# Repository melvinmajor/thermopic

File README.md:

# ThermoPIC

1st project of the academic year for the lesson of digital electronics 2nd Bachelor at EPHEC Louvain-la-Neuve

## Our Team

Our group number is: **1**

Our team is composed of 4 people :

- Melvin Campos Casares (_**@melvinmajor**_)
- Maxime De Cock (_**@maxicosi**_)
- Guillaume Vanden Herrewegen (_**@guivdh**_)
- Hubert Van De Walle (_**@HE201496**_)

We use Trello to manage our teamwork : [Trello - ThermoPic project](https://trello.com/b/enrK0mAl/thermopic-project).

## ThermoPIC

ThermoPIC is a project for the lesson of digital electronics.
In this project, we're working with the 18F458 PIC (High-Performance, Enhanced Flash Microcontrollers with CAN Module).
You will find some documentation inside the [doc](doc/) folder.

We're working with 2 programming languages :

- C
- Java

## License

This project is licensed under the GNU General Public License v3.0 - see the [LICENSE](LICENSE.md) file for details.

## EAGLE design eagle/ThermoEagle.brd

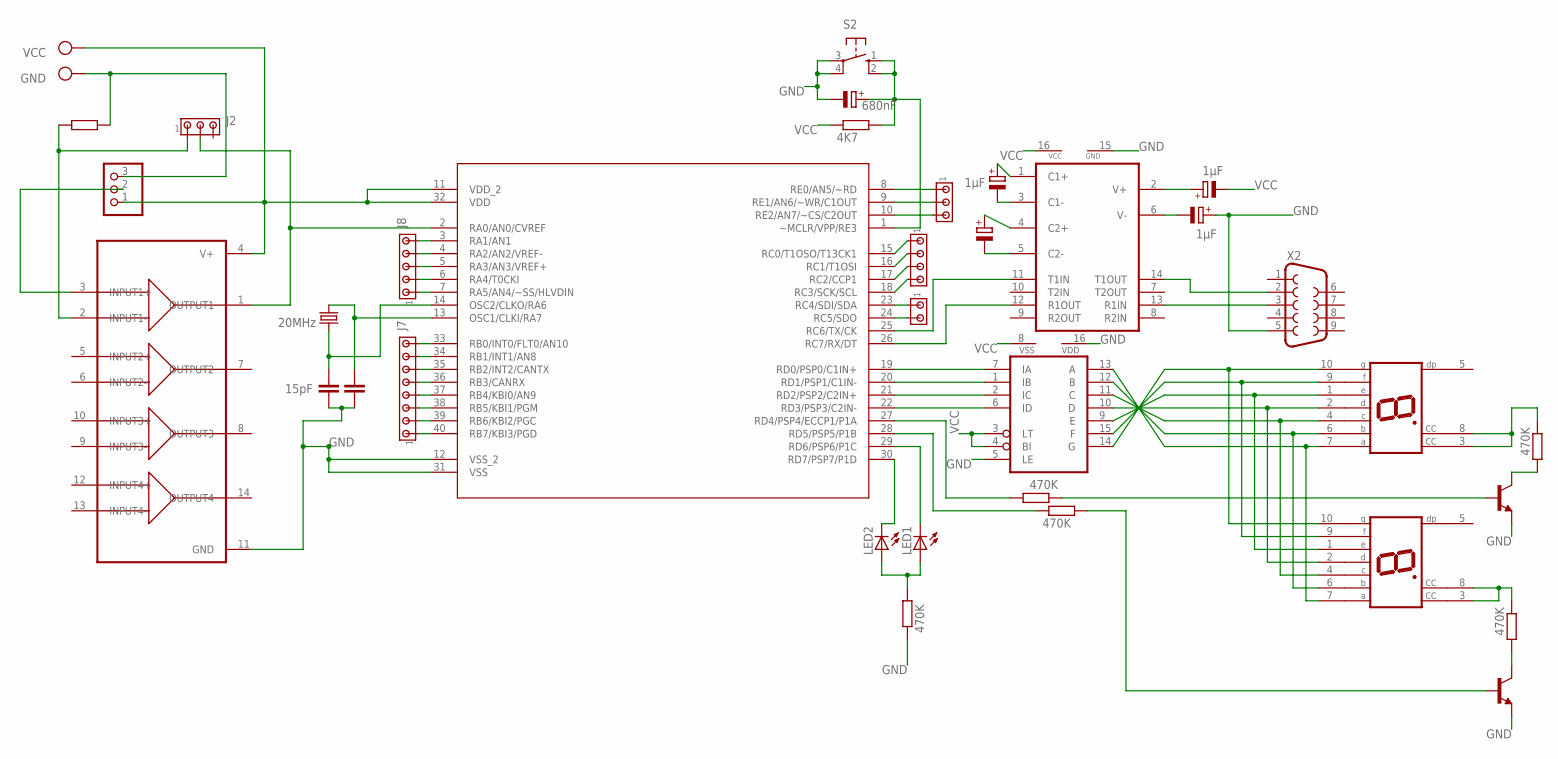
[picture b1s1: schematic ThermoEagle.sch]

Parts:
C1, C2, C3, C5: 1µF; B45181B
C6: 15pF; C050-025X075
C7: C-EU050-025X075; C050-025X075
C8: 680nF; B45181C
DIS1, DIS2: HD-H103; HDSP-M
IC1: MAX232; DIL16
IC2: 4511N; DIL16
J1: MTA04-100; 10X04MTA
J2, J4: MTA03-100; 10X03MTA
J3: MTA02-100; 10X02MTA
J7: MTA08-100; 10X08MTA
J8: MTA05-100; 10X05MTA
JP1: PINHD-1X3; 1X03
LED1, LED2: LED_ELD260; LED_LD260
Q1: 20MHz; HC18U-V
R1, R2, R3, R10, R11: 470K; 0207/7
R13: R-EU_0207/7; 0207/7
R14: 4K7; 0207/7
S2: 10-XX; B3F-10XX
T1, T2: 2N2219; TO5
U1: LM324; DIP790W51P254L1994H508Q14
U$1: PIC18F4585-I/P; DIP254P1524X635-40
X1: AK300/2
X2: F09VB

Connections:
GND: C3.+, C6.2, C7.2, C8.-, IC1.15 (GND), IC2.5 (LE), IC2.16 (VDD), JP1.3, R1.1, R13.1, S2.3, S2.4 (P1), T1.1 (E), T2.1 (E), U1.11 (GND), U$1.12 (VSS_2), U$1.31 (VSS), X1.2, X2.5
unnamed: IC2.7 (IA), U$1.19 (RD0/PSP0/C1IN+)
unnamed: IC1.14 (T1OUT), X2.2
unnamed: R11.2, T1.2 (B)
unnamed: R10.2, T2.2 (B)
unnamed: IC2.1 (IB), U$1.20 (RD1/PSP1/C1IN-)
unnamed: DIS1.3 (CC), DIS1.8 (CC), R3.1
unnamed: R2.2, T1.3 (C)
unnamed: DIS1.9 (F), DIS2.9 (F), IC2.15 (F)
unnamed: IC2.2 (IC), U$1.21 (RD2/PSP2/C2IN+)
unnamed: DIS2.3 (CC), DIS2.8 (CC), R2.1
unnamed: C1.+, IC1.1 (C1+)
unnamed: C1.-, IC1.3 (C1-)
unnamed: C5.+, IC1.4 (C2+)
unnamed: C5.-, IC1.5 (C2-)
unnamed: C2.+, IC1.2 (V+)
unnamed: C3.-, IC1.6 (V-)
unnamed: IC1.13 (R1IN), X2.3
unnamed: IC2.6 (ID), U$1.22 (RD3/PSP3/C2IN-)
unnamed: LED1.A, LED2.A, R1.2
unnamed: DIS1.1 (E), DIS2.1 (E), IC2.9 (E)
unnamed: DIS1.2 (D), DIS2.2 (D), IC2.10 (D)
unnamed: DIS1.4 (C), DIS2.4 (C), IC2.11 (C)
unnamed: DIS1.6 (B), DIS2.6 (B), IC2.12 (B)
unnamed: DIS1.7 (A), DIS2.7 (A), IC2.13 (A)
unnamed: R3.2, T2.3 (C)
unnamed: J2.1, R13.2, U1.2 (INPUT1-)
unnamed: J8.5, U$1.3 (RA1/AN1)
unnamed: J8.4, U$1.4 (RA2/AN2/VREF-)
unnamed: J8.3, U$1.5 (RA3/AN3/VREF+)
unnamed: J8.2, U$1.6 (RA4/T0CKI)
unnamed: DIS1.10 (G), DIS2.10 (G), IC2.14 (G)
unnamed: LED2.K (C), U$1.30 (RD7/PSP7/P1D)
unnamed: R10.1, U$1.27 (RD4/PSP4/ECCP1/P1A)
unnamed: IC1.11 (T1IN), U$1.25 (RC6/TX/CK)
unnamed: R11.1, U$1.28 (RD5/PSP5/P1B)
unnamed: LED1.K (C), U$1.29 (RD6/PSP6/P1C)
unnamed: J8.1, U$1.7 (RA5/AN4/~SS/HLVDIN)
unnamed: JP1.2, U1.3 (INPUT1+)
unnamed: J2.2, U1.1 (OUTPUT1), U$1.2 (RA0/AN0/CVREF)
unnamed: J7.8, U$1.33 (RB0/INT0/FLT0/AN10)
unnamed: J7.7, U$1.34 (RB1/INT1/AN8)
unnamed: C6.1, Q1.1, U$1.14 (OSC2/CLKO/RA6)
unnamed: C7.1, Q1.2, U$1.13 (OSC1/CLKI/RA7)
unnamed: J7.6, U$1.35 (RB2/INT2/CANTX)
unnamed: J7.5, U$1.36 (RB3/CANRX)
unnamed: J7.4, U$1.37 (RB4/KBI0/AN9)
unnamed: J7.3, U$1.38 (RB5/KBI1/PGM)
unnamed: J7.2, U$1.39 (RB6/KBI2/PGC)
unnamed: J7.1, U$1.40 (RB7/KBI3/PGD)
unnamed: J4.1, U$1.8 (RE0/AN5/~RD)
unnamed: J4.2, U$1.9 (RE1/AN6/~WR/C1OUT)
unnamed: J4.3, U$1.10 (RE2/AN7/~CS/C2OUT)
unnamed: J1.1, U$1.15 (RC0/T1OSO/T13CK1)
unnamed: J1.2, U$1.16 (RC1/T1OSI)
unnamed: J1.3, U$1.17 (RC2/CCP1)
unnamed: J1.4, U$1.18 (RC3/SCK/SCL)
unnamed: J3.1, U$1.23 (RC4/SDI/SDA)
unnamed: J3.2, U$1.24 (RC5/SDO)
unnamed: C8.+, R14.2, S2.1 (S), S2.2 (S1), U$1.1 (~MCLR/VPP/RE3)
RX: IC1.12 (R1OUT), U$1.26 (RC7/RX/DT)
VCC: C2.-, IC1.16 (VCC), IC2.3 (LT), IC2.4 (BI), IC2.8 (VSS), JP1.1, R14.1, U1.4 (V+), U$1.11 (VDD_2), U$1.32 (VDD), X1.1

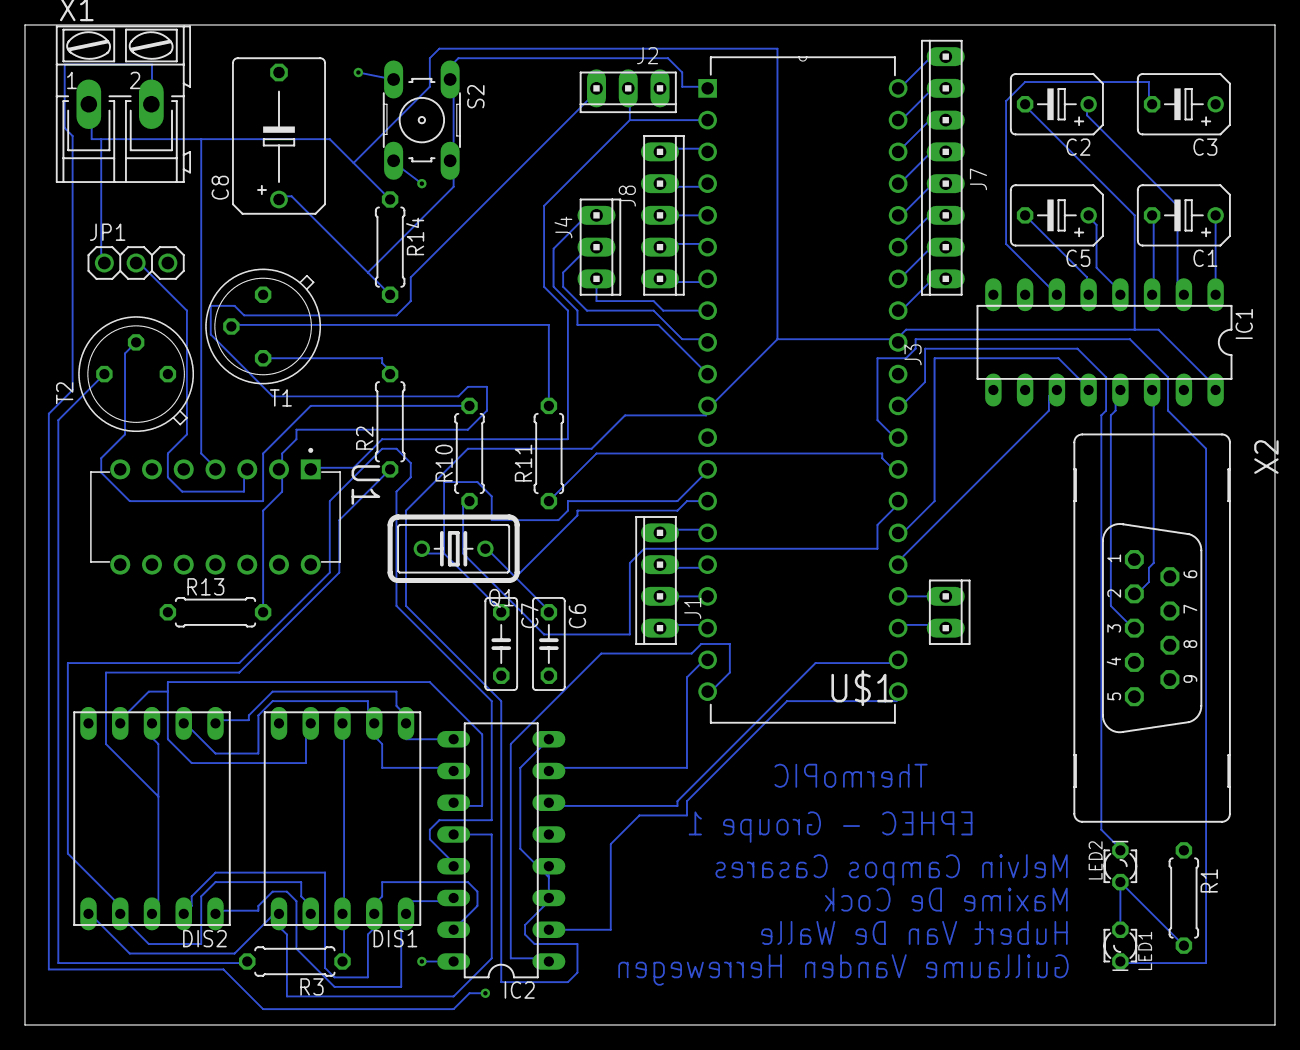
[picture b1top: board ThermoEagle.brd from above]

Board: 2 copper layers, 100.0 x 80.0 mm, 35 parts (0 on the bottom side), 62 nets.

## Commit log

2019-02-04 Add some useful datasheet
    LM324, LM35, PIC 18F458 (and PIC 16F877 which is optional).
2019-02-06 Update LICENSE and README
    Add private Trello link.
    GPL3 License
2019-02-08 Add specs and evaluation grid
2019-02-16 Create ThermoEagle.sch
    schéma eagle, peut-être besoin de retouche
2019-02-17 Change eagle folder name
2019-02-17 Add some other useful datasheet
    LM35, MAX232.
    Remove unnecessary LM350.
2019-02-17 Create ThermoProteus.pdsprj
    ajout du dossier proteus et du fichier ThermoProteus
2019-02-18 Rename Proteus folder to lower case
2019-02-18 Create Eagle .brd file
    Create ThermoEagle.brd but still needs to be done.
2019-02-21 changement du schéma eagle et proteus
    dernier ajout ou changement du montage
2019-02-26 Update ThermoEagle board
    Updated the board to match the new Schematic file from Eagle.
    Made the blue circuit but still need to perform the mass.
2019-02-26 Eagle to fix by Maxime
2019-02-26 eagle
    - ajustement de la DB9
    - connection d'un connecteur à trois branche
    - suppression de résistance
2019-02-28 Remove unnecessary shit
2019-02-28 Update .gitignore
    Temporary files from Eagle now listed and Fix wrong spelling folder names by @maxicosi on Eagle and Proteus.
2019-02-28 Final update ThermoEagle board... I hope
2019-03-09 Update .brd file (now has isolation)
2019-03-09 connector
    ajout des connecteurs, pour les parties non connectées
2019-03-09 Final update ThermoEagle board
    With connectors for parts that aren't connected + isolation
2019-03-09 Create code.c
    code qui permet d'afficher sur les 2 digits l'entrée analogique (fonctionnel mais pas correcte car la valeur affichée n'est pas la bonne)
2019-03-10 Erreur corrigé
2019-03-10 Update ThermoEagle board
2019-03-10 Update rapport-intermediaire #ri1
    First idea of introduction and some other additions
2019-03-10 Text correction in rapport-intermediaire.md
2019-03-10 Update rapport-intermediaire.md
    - Add some personal content,
    - Quick correction of the overall text,
    - Addition of pcb and schematic screenshot.
2019-03-10 Update rapport-intermediaire #ri2
    Update some dates in order to match reality.
2019-03-10 Update rapport-intermediaire.md
    rajout de mes attentes et objectifs
2019-03-10 Update README.md
    Add group number
2019-03-10 Update pcb screenshot
2019-03-10 Update rapport-intermediaire.md
    Add group number
2019-03-10 Update rapport-intermediaire.md #ri3
2019-03-10 Add my own conclusion
2019-03-10 Update rapport-intermediaire.md
    Addition of some content about the planning.
2019-03-10 Update rapport-intermediaire.md #ri4
    - Remove "Applications" header,
    - Correction of some misspellings and typos,
    - Add new proteus schema.
2019-03-11 Update rapport-intermediaire.md #ri5
    - Add conclusion,
    - Delete the * before .brd (makes bad things on VIM).
2019-03-11 Update ThermoEagle board #IamBRD
    Once more updated but still needs further improvements I think...
    Maxime needs to perform a complete analysis if because there are lots of
    things not connected to GND or VCC !
2019-03-11 Update PCB image
2019-03-11 Update Eagle files (schema + board)
    I hope this time it's the final update.
    - Added GND and VCC labels for componenets Maxime had forgotten,
    - Updated board with new routes, etc.
2019-03-11 Update PCB image + Add isolated PCB image
2019-03-11 Update board... idk
    Moved the alimentation port in a right place and in the right
    orientation.
2019-03-11 Update PCB image + isolated PCB image
2019-03-11 Update pandoc config
2019-03-11 Fix pandoc config colors
2019-03-11 Fix last name of Maxime
2019-03-11 Update rapport-intermediaire.md - FINAL
2019-03-11 push pdf
2019-03-11 Update Board - validation #2 by EuroCircuit
2019-03-11 Temporary update for PCB
2019-03-12 Fix brd file
    It's now accepted by EuroCircuit and the teacher launched the print
    order.
2019-05-14 Firs stage of final report
2019-05-14 Second stage of final report
    Inserted all content coming from intermediary report that can be reused.
2019-05-14 Update final report
2019-05-14 Moved C code into a directory
2019-05-14 Added all files necessary for C part of the project
2019-05-17 Minor update rapport-final.md
2019-05-19 Update final report
    Corrected new part added by Guillaume.
    Added some content in order to complete the report as much as possible.
2019-05-19 Add bibliography in final report
2019-05-19 Update final report (bibliography, java part)
2019-05-19 Update rapport-final.md
    ajout de ma conclusion personnelle
2019-05-20 Add java
2019-05-20 Fix mistakes and trailing whitespace
2019-05-20 Add ccl
2019-05-20 Final update of rapport-final.md
2019-05-20 Update final report based on Pandoc config
2019-05-20 Add rapport-final.pdf

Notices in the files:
parts and their libraries:
SparkFun-Connectors: Licensing: Creative Commons ShareAlike 4.0 International - https://creativecommons.org/licenses/by-sa/4.0
